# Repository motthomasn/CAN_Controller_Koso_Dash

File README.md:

# CAN_Controller_Koso_Dash
Teensy 3.2 based controller board designed to recieve engine data from ECU via CAN-Bus and use it to control a Koso RX2N motorcycle dash

This module was built for my CBR250RRi project. The aim was to run my aftermarket Koso RX2N dash using the same sensors (coolant & oil temp) as the ECU to avoid having to double up on sensors. The idea was to recieve all necessary signals from the ECU via CAN-Bus and then have the Teensy replicate the analogue signals that the dash expects.

The Koso RX2N dash has the following possible inputs for indication:
1. Engine speed         - variable frequency square wave signal
1. Vehicle speed        - variable frequency square wave signal
1. Coolant temperature  - thermistor
1. Oil temperature      - thermistor
1. Oil pressure light   - digital on/off signal, low side switch
1. EOBD light           - digital on/off signal, low side switch
1. Neutral light        - digital on/off signal, low side switch
1. Fuel level           - digital on/off signal, low side switch
1. Hi-beam light        - digital on/off signal, high side switch
1. RH Indicator         - digital on/off signal, high side switch
1. LH Indicator         - digital on/off signal, high side switch

The LH/RH indicators, hi-beam, fuel level & neutral signals were all provided directly from the sensors and wire harness. All other signals relied on sensors which would be connected directly to the ECU and therefore required the controller to provide the signals based on data recieved via CAN-Bus.

**Engine & Vehicle Speed**
Although the ECU could provide the required signal directly to the dash using an injector output, I decided to save the ECU output and hand the job over to the dash controller. A 50% duty cycle variable frequency signal is provided by the Teensy switching 12V to gound. The frequency is updated at 50Hz to avoid visible stuttering of the dash needle during fast engine speed ramps. 
A similar tactic as engine speed was employed to the vehicle speed signal apart from the signal being 5V level and the signal frequency is updated at only 5Hz as vehicle speed is displayed on a 7-segment display. 

**Coolant & Oil Temperature**
A pair of digital potentiometers are employed to replicate the thermistor resistance. The R-T curve for the sensors supplied with the RX2N had been provided by Koso tech support. The linear response and resolution of the digital potentiometers means that there could be an error of up to 3°C between the actual and displayed values between 90-110°C temperature. The dash display is only an indication so this level of accuracy is acceptable.

**Oil Pressure Light**
My bike and most others from the 1990's came fitted with an oil pressure switch. The original switch could be connected directly to the dash but as I have replaced the pressure switch with an actual pressure sensor, I have added the possibility of controlling the light via the dash controller. In the current version of the code, the actual oil pressure is compared to a single threshold, so operates the light much the same as the original switch. I plan to update the code to add a varying pressure threshold with engine speed and oil temperature after I have collected some data to build a normal oil pressure map.

**EOBD Light**
The EOBD light is a handy indicator of something being wrong on the ECU side. The measure of "something wrong" depends on the ECU but on my Life Racing F88R I use a flag called *engineEnable* and set the EOBD light if the flag is not equal to 0 (OK).

I included tracks on the controller board for USB to allow the Teensy code to be updated without opening the enclosure. However, I did not adhere to recommendations around USB bus design and so this does not work. I plan to update the board to meet guidelines in the future.

For further details on the CBR250RRi project, refer to the website https://www.cbr250rri.com/.

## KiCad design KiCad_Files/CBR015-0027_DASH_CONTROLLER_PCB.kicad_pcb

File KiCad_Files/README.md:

This folder contains the KiCad files for the Dash Controller Module

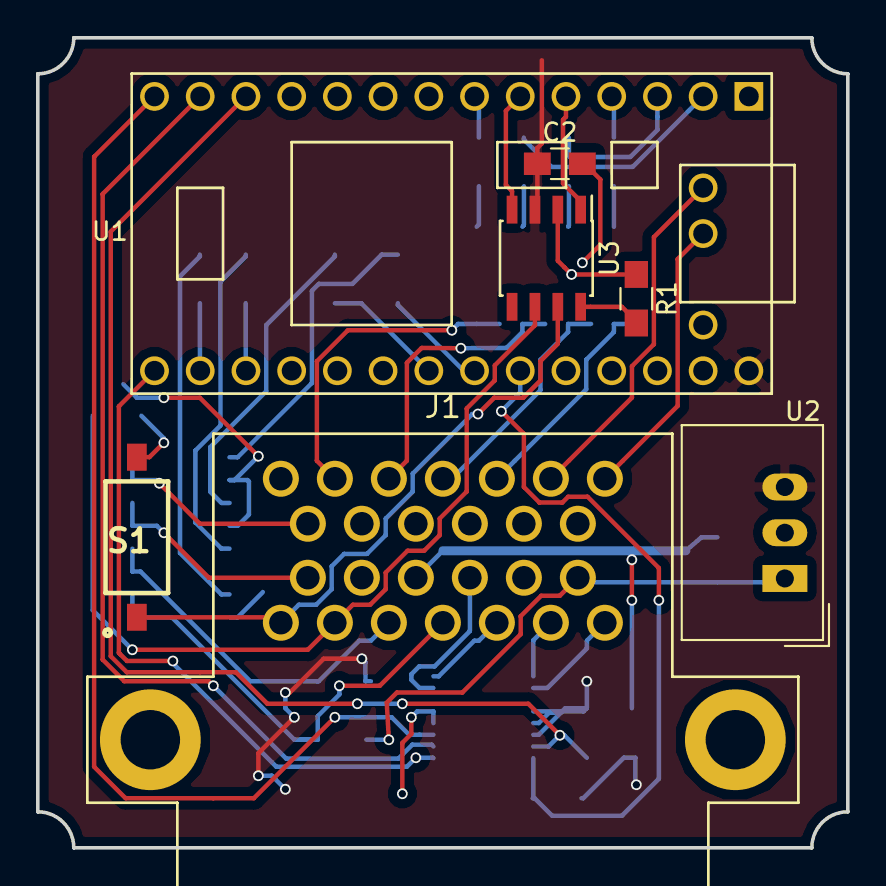
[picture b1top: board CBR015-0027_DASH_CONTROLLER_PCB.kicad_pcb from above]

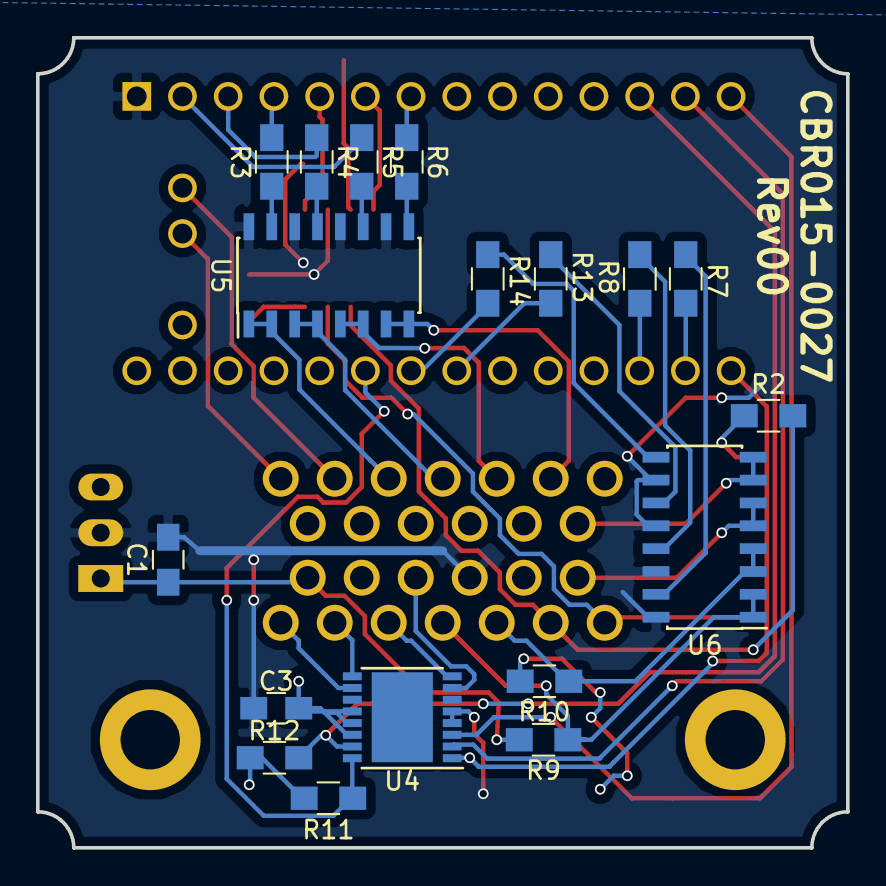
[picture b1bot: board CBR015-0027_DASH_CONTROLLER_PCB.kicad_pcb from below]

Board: 2 copper layers, 45.0 x 45.0 mm, 25 parts (18 on the bottom side), 44 nets.

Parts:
C1: 22µF; C_0805_HandSoldering
C2, C3: 100nF; C_0805_HandSoldering
J1: Conn_02x13_Odd_Even; TE_SUPERSEAL_1.0_26-WAY
R1: 18K; R_0805_HandSoldering
R2: 120; R_0805_HandSoldering
R3, R4, R5, R6, R7, R8, R13, R14: 523; R_0805_HandSoldering
R9, R10: 10K; R_0805_HandSoldering
R11, R12: 2.2K; R_0805_HandSoldering
S1: IKD0103101
U1: TEENSY_3.2_BASIC_W_USB
U2: TSR_1-2450; DCDC-Conv_TRACO_TSR-1
U3: MCP2551-I-SN; SOIC-8_3.9x4.9mm_Pitch1.27mm
U4: AD5235; HTSSOP-16-1EP_4.4x5mm_Pitch0.65mm
U5, U6: MMPQ3904; SOIC-16_3.9x9.9mm_Pitch1.27mm

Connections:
+5V: C2.1, C3.1, R10.2, R11.1, R12.1, U1.28, U2.3, U3.3, U4.12, U4.13, U4.14
+12V: C1.1, J1.8, R9.2, U2.1
BASE_B: R3.1, U1.4
BASE_EOBD: R13.1, U1.21
BASE_G: R6.1, U1.7
BASE_OILP: R14.1, U1.22
BASE_R: R4.1, U1.3
BASE_TACH: R7.1, U1.16
BASE_VSS: R8.1, U1.17
BASE_Y: R5.1, U1.2
CANH: J1.7, S1.1, U3.7
CANL: J1.6, R2.1, U3.6
CLT_GND: J1.3, U4.8
CLT_T: J1.10, U4.7
EOBD: J1.13, U6.5, U6.6
Earth: C1.2, C2.2, C3.2, J1.11, R1.1, U1.1, U2.2, U3.2, U4.4, U4.5, U5.10, U5.12, U5.14, U5.16, U6.10, U6.12, U6.14, U6.16
unnamed: R1.2, U3.8
unnamed: R3.2, U5.15
unnamed: R4.2, U5.13
unnamed: R5.2, U5.11
unnamed: R6.2, U5.9
unnamed: R7.2, U6.15
unnamed: R8.2, U6.13
unnamed: R13.2, U6.11
unnamed: R14.2, U6.9
OIL_GND: J1.2, U4.9
OIL_P: J1.19, U6.7, U6.8
OIL_T: J1.1, U4.10
POT_CS: R12.2, U1.12, U4.15
POT_RDY: R11.2, U1.23, U4.16
RX_CAN: U1.6, U3.4
SHIFT_B: J1.22, U5.1, U5.2
SHIFT_G: J1.25, U5.7, U5.8
SHIFT_R: J1.23, U5.3, U5.4
SHIFT_Y: J1.24, U5.5, U5.6
SPI_DIN: U1.14, U4.3
SPI_DOUT: U1.13, U4.2
SPI_SCK: U1.15, U4.1
TACH: J1.4, R9.1, U6.1, U6.2
TERML: R2.2, S1.2
TX_CAN: U1.5, U3.1
USB_D+: J1.21, U1.29
USB_D-: J1.20, U1.30
VSS: J1.5, R10.1, U6.3, U6.4

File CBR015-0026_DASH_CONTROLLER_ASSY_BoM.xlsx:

Designation | Qty | Description | Value | Manufacturer | Part Number | Package | Supplier | Stock No. / Order Code | Notes | Datasheet
U1 | 1 | Teensy 3.2 |  | PJRC | Teensy 3.2 | PDIP
 | 2 | Teensy Pin Header | 14-way, 2.54mm |  |  |  | RS
 | 2 | Teensy Connector Socket | 14-way, 2.54mm |  |  |  | RS
 | 1 | Teensy USB Pin Header |  |  |  |  | RS
 | 1 | Teensy USB Connector Socket |  |  |  |  | RS
U2 | 1 | 5V Power Regulator | 5V, 1A | Traco Power | TSR-1-2450 | SIP3 | RS | 666-4379
U3 | 1 | CAN Transciever |  | Microchip | MCP2551-I/SN | SOIC-8 | RS | 738-6036
U4 | 1 | Digital Potentiometer | 250K, 1024-posn | Analog Devices | AD5235BRUZ250 | TSSOP-16 | RS | 497-0751
U5, U6 | 2 | Dash Signal & Shift Light Switches | NPN, 40V, 200mA | ON Semiconductor | MMPQ3904 | SOIC-16 | RS | 807-4863
C1 | 1 | Power Reg Cap | 22uF | Murata | GRM219B30G226ME66D | 0805 | RS | 798-4621
C2 | 1 | CAN Transciever Smoothing Cap | 100nF | AVX | 08055C104KAT2A | 0805 | RS | 464-6688
C3 | 1 | Digital Pot Smoothing Cap | 100nF | AVX | 08055C104KAT2A | 0805 | RS | 464-6688
R1 | 1 | CAN Transciever Reset | 18K | TE Connectivity | CRG0805F18K | 0805 | RS | 223-0590
R2 | 1 | CAN Termination | 120 | Panasonic | ERJP06F1200V | 0805 | RS | 721-7674
R3, R4, R5, R6, R7, R8, R13, R14 | 8 | BJT Base Current Limiters | 523 | Panasonic | ERA6AEB5230V | 0805 | RS | 708-6048
R9, R10 | 2 | VSS & TACH Pull-up Resistors | 10K | TE Connectivity | CRG0805F10K | 0805 | RS | 223-0562
R11, R12 | 2 | Pot RDY & CS Pull-up resistors | 2.2K | Vishay | CRCW08052K20FKEA | 0805 | RS | 679-1207
S1 | 1 | CAN Termination Jumper | Single SPST | APEM | IKD0103101 |  | RS | 877-2233
J1 | 1 | Harness Connector | Superseal 1.0, 26-way | TE Connectivity | 6437288-4 |  | RS | 726-7011

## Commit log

2020-09-20 PlatformIO Project
2023-06-13 Update main.cpp to v2.0
    CAN IDs updated to match CBR250RRi CAN config v3.0 and shift lights functionality added
2025-11-04 Update to v3.0 code
